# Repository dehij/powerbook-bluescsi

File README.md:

BlueSCSI PowerBook edition by dehij
v2 version

This BlueSCSI board is designed and tested with Macintosh PowerBooks (tested on 140 and 145B).

Differences with v1:
- uses 1206 SMD termination resistors (18x 220 ohm, 18x 330 ohm)
- uses a different microSD card slot which is easier to find online

Uses the following external footprints:

STM32 BluePill symbol and footprint:
https://github.com/yet-another-average-joe/Kicad-STM32

push-push microSD card footprint by @Joan_Sparky and used with permission. (found in: Other footprints/)

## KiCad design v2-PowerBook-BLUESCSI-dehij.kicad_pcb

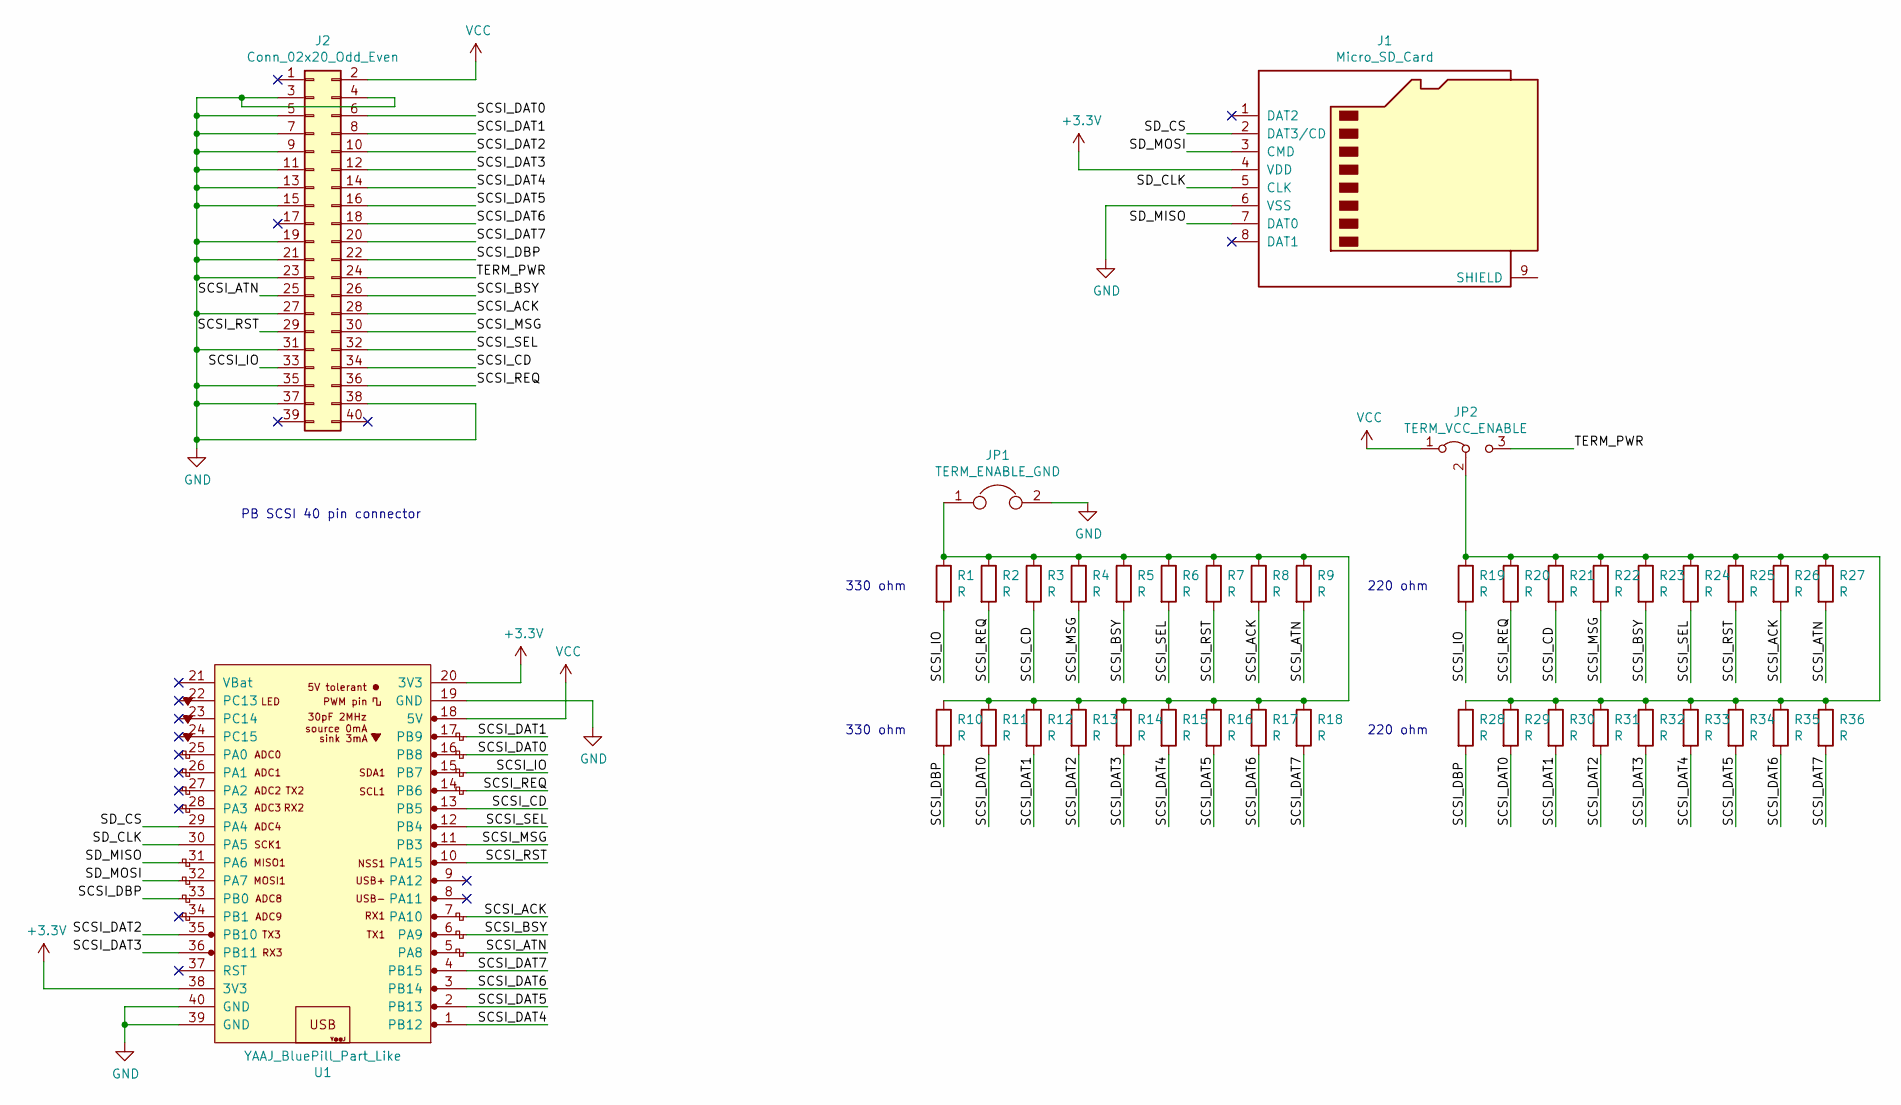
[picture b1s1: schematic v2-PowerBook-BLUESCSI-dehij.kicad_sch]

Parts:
J1: Micro_SD_Card; Conn_uSDcard
J2: Conn_02x20_Odd_Even; PinSocket_2x20_P2.00mm_Vertical
JP1: TERM_ENABLE_GND; SolderJumper-2_P1.3mm_Bridged_Pad1.0x1.5mm
JP2: TERM_VCC_ENABLE; SolderJumper-3_P1.3mm_Bridged12_Pad1.0x1.5mm_NumberLabels
R1, R2, R3, R4, R5, R6, R7, R8, R9, R10, R11, R12, R13, R14, R15, R16, R17, R18, R19, R20, R21, R22, R23, R24, R25, R26, R27, R28, R29, R30, R31, R32, R33, R34, R35, R36: R; R_1206_3216Metric_Pad1.30x1.75mm_HandSolder
U1: YAAJ_BluePill_Part_Like; YAAJ_BluePill_2

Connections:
+3V3: J1.4 (VDD), U1.20 (3V3), U1.38 (3V3)
/SCSI_ACK: J2.28, R8.2, R26.2, U1.7 (PA10)
/SCSI_ATN: J2.25, R9.2, R27.2, U1.5 (PA8)
/SCSI_BSY: J2.26, R5.2, R23.2, U1.6 (PA9)
/SCSI_CD: J2.34, R3.2, R21.2, U1.13 (PB5)
/SCSI_DAT0: J2.6, R11.2, R29.2, U1.16 (PB8)
/SCSI_DAT1: J2.8, R12.2, R30.2, U1.17 (PB9)
/SCSI_DAT2: J2.10, R13.2, R31.2, U1.35 (PB10)
/SCSI_DAT3: J2.12, R14.2, R32.2, U1.36 (PB11)
/SCSI_DAT4: J2.14, R15.2, R33.2, U1.1 (PB12)
/SCSI_DAT5: J2.16, R16.2, R34.2, U1.2 (PB13)
/SCSI_DAT6: J2.18, R17.2, R35.2, U1.3 (PB14)
/SCSI_DAT7: J2.20, R18.2, R36.2, U1.4 (PB15)
/SCSI_DBP: J2.22, R10.2, R28.2, U1.33 (PB0)
/SCSI_IO: J2.33, R1.2, R19.2, U1.15 (PB7)
/SCSI_MSG: J2.30, R4.2, R22.2, U1.11 (PB3)
/SCSI_REQ: J2.36, R2.2, R20.2, U1.14 (PB6)
/SCSI_RST: J2.29, R7.2, R25.2, U1.10 (PA15)
/SCSI_SEL: J2.32, R6.2, R24.2, U1.12 (PB4)
/SD_CLK: J1.5 (CLK), U1.30 (PA5)
/SD_CS: J1.2 (DAT3/CD), U1.29 (PA4)
/SD_MISO: J1.7 (DAT0), U1.31 (PA6)
/SD_MOSI: J1.3 (CMD), U1.32 (PA7)
/TERM_PWR: J2.24, JP2.3 (B)
GND: J1.6 (VSS), J2.3, J2.4, J2.5, J2.7, J2.9, J2.11, J2.13, J2.15, J2.19, J2.21, J2.23, J2.27, J2.31, J2.35, J2.37, J2.38, JP1.2, U1.19 (GND), U1.39 (GND), U1.40 (GND)
unnamed: JP1.1, R1.1, R2.1, R3.1, R4.1, R5.1, R6.1, R7.1, R8.1, R9.1, R10.1, R11.1, R12.1, R13.1, R14.1, R15.1, R16.1, R17.1, R18.1
unnamed: JP2.2 (C), R19.1, R20.1, R21.1, R22.1, R23.1, R24.1, R25.1, R26.1, R27.1, R28.1, R29.1, R30.1, R31.1, R32.1, R33.1, R34.1, R35.1, R36.1
VCC: J2.2, JP2.1 (A), U1.18 (5V)

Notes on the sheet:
PB SCSI 40 pin connector
330 ohm
220 ohm
220 ohm

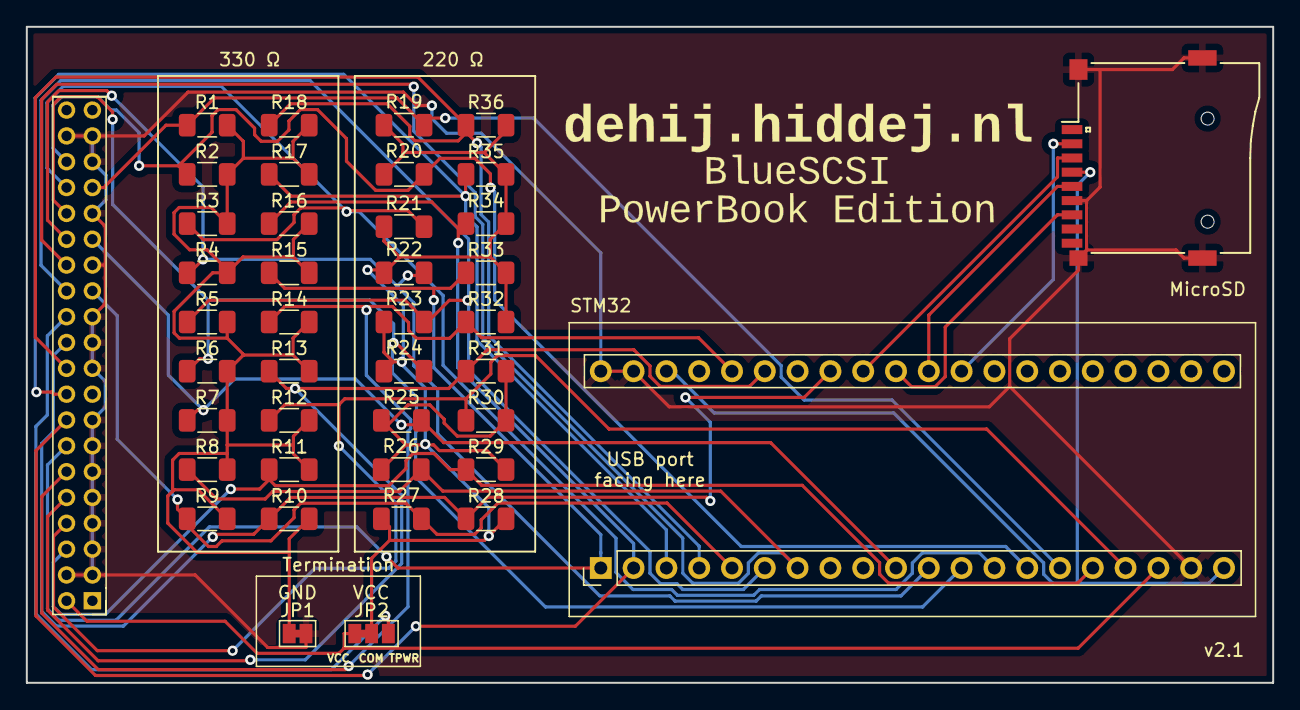
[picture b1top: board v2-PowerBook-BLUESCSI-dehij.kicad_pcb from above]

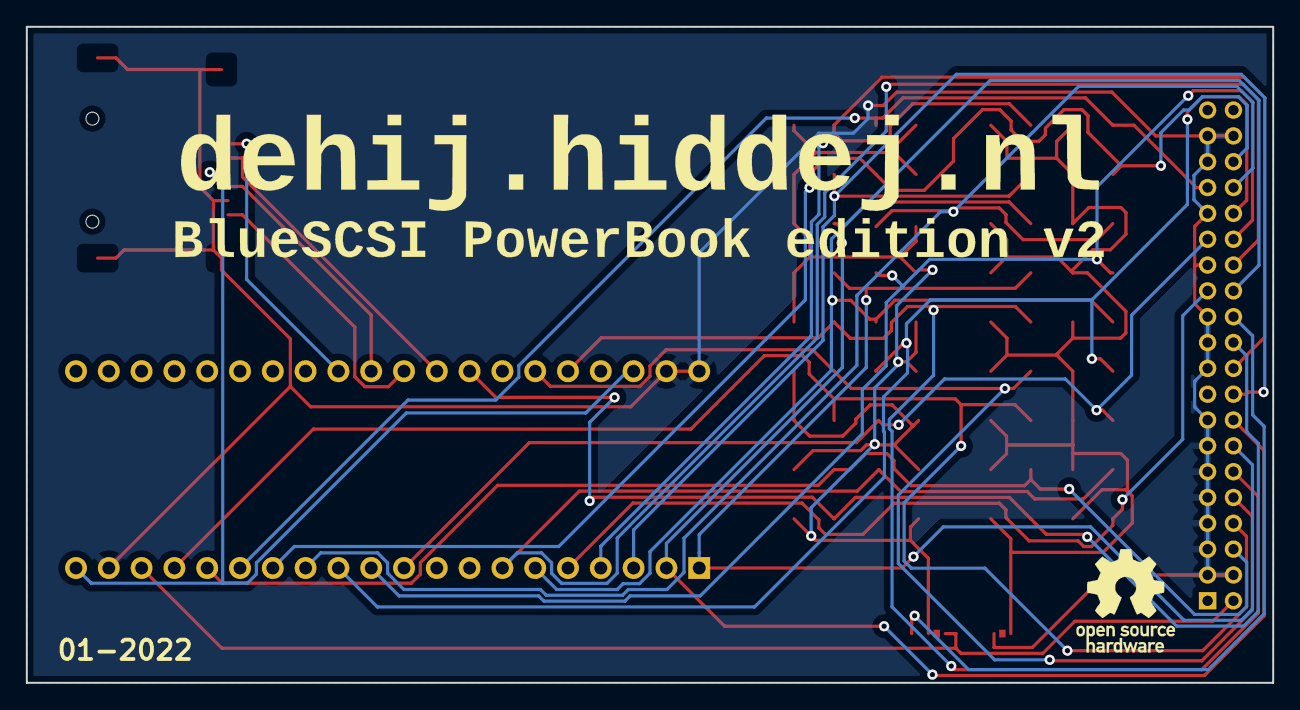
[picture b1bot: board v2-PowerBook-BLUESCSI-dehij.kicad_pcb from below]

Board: 2 copper layers, 96.5 x 50.8 mm, 43 parts (2 on the bottom side), 28 nets.

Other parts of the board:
G1: LOGO; Backsilkscreen
G2: LOGO; PBlogo2

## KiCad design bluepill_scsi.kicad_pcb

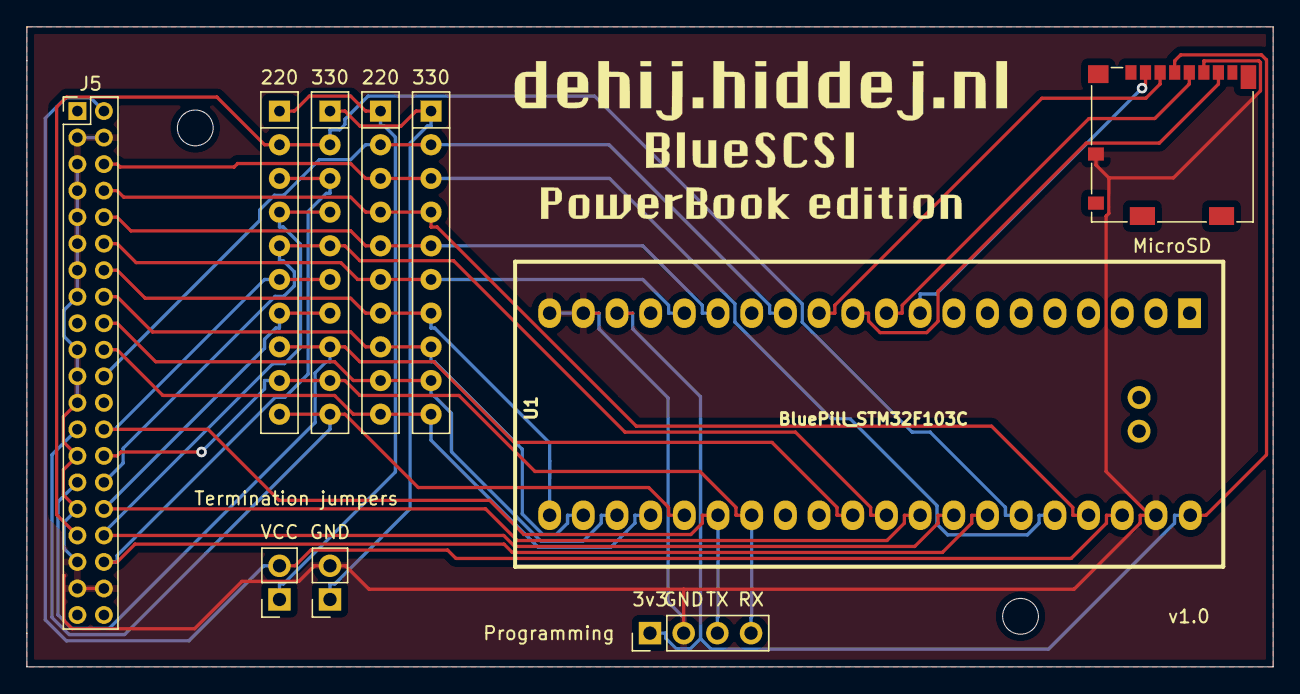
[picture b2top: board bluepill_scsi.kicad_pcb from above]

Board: 2 copper layers, 94.0 x 48.3 mm, 12 parts (0 on the bottom side), 27 nets.

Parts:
H1, H2: MountingHole_Pad; MountingHole_2.7mm_M2.5
J3: Programming Pins; PinHeader_1x04_P2.54mm_Vertical
J5: Conn_02x20_Odd_Even; PinHeader_2x20_P2.00mm_Vertical
JP1: TERM_ENABLE_GND; PinSocket_1x02_P2.54mm_Vertical
JP2: TERM_ENABLE_5V; PinSocket_1x02_P2.54mm_Vertical
MicroSD: Micro_SD_Card; microSD_HC_Molex_104031-0811
RN1, RN3: 220; R_Array_SIP10
RN2, RN4: 330; R_Array_SIP10
U1: BluePill_STM32F103C

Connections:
+3V3: J3.1, MicroSD.4, U1.18, U1.40
/SCSI_ACK: J3.4, J5.28, RN1.9, RN2.9, U1.27
/SCSI_ATN: J5.25, RN1.10, RN2.10, U1.25
/SCSI_BSY: J3.3, J5.26, RN1.6, RN2.6, U1.26
/SCSI_CD: J5.34, RN1.4, RN2.4, U1.33
/SCSI_DAT0: J5.6, RN3.3, RN4.3, U1.36
/SCSI_DAT1: J5.8, RN3.4, RN4.4, U1.37
/SCSI_DAT2: J5.10, RN3.5, RN4.5, U1.15
/SCSI_DAT3: J5.12, RN3.6, RN4.6, U1.16
/SCSI_DAT4: J5.14, RN3.7, RN4.7, U1.21
/SCSI_DAT5: J5.16, RN3.8, RN4.8, U1.22
/SCSI_DAT6: J5.18, RN3.9, RN4.9, U1.23
/SCSI_DAT7: J5.20, RN3.10, RN4.10, U1.24
/SCSI_DBP: J5.22, RN3.2, RN4.2, U1.13
/SCSI_IO: J5.33, RN1.2, RN2.2, U1.35
/SCSI_MSG: J5.30, RN1.5, RN2.5, U1.31
/SCSI_REQ: J5.36, RN1.3, RN2.3, U1.34
/SCSI_RST: J5.29, RN1.8, RN2.8, U1.30
/SCSI_SEL: J5.32, RN1.7, RN2.7, U1.32
/SD_CLK: MicroSD.5, U1.10
/SD_CS: MicroSD.2, U1.9
/SD_MISO: MicroSD.7, U1.11
/SD_MOSI: MicroSD.3, U1.12
GND: J3.2, J5.3, J5.4, J5.5, J5.7, J5.9, J5.11, J5.13, J5.15, J5.19, J5.21, J5.23, J5.27, J5.31, J5.35, J5.37, J5.38, JP1.2, MicroSD.6, MicroSD.9, U1.19, U1.20, U1.39
unnamed: JP1.1, RN2.1, RN4.1
unnamed: JP2.1, RN1.1, RN3.1
VCC: J5.2, JP2.2, U1.38

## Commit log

2021-09-29 Add GPL
2021-09-30 Add V1 files
2022-05-03 Add V2 files
    Deleted v1 and added v2 board revision.
